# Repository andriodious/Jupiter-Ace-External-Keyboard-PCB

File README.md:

# Jupiter-Ace-External-Keyboard-PCB

Allows an external keyboard to be built for a Jupiter Ace micro. Inspiration for this board came from:
https://www.jupiter-ace.co.uk/custom_aces_CN_IBMACE.html

The measurements for this keyboard allow the fitting of Cherry Part Number: MX1A-L1NN key switches.

The board has also been fitted into a DK-Tronics keyboard case : https://t-lcarchive.org/dktronics-keyboard/

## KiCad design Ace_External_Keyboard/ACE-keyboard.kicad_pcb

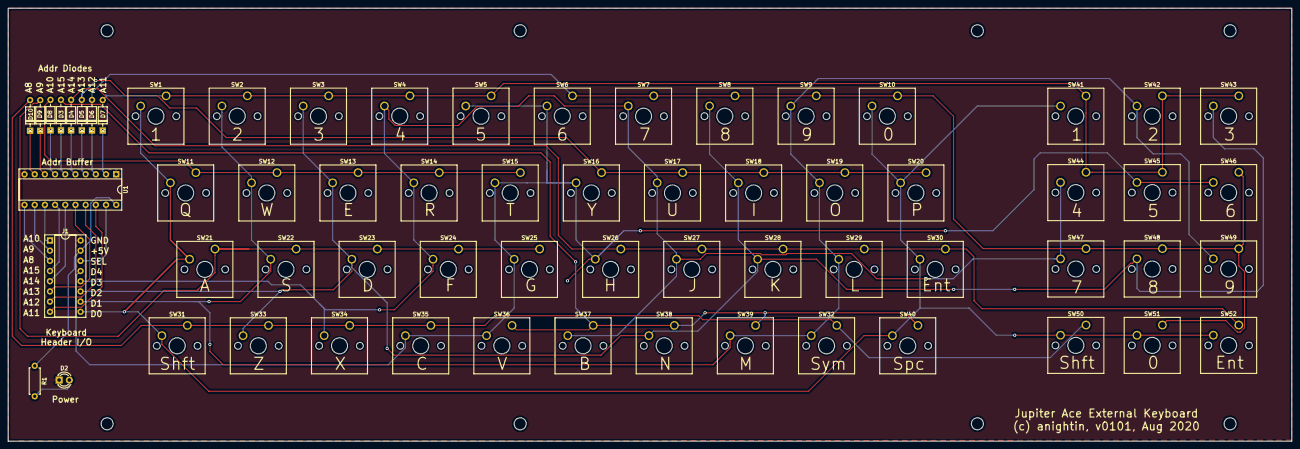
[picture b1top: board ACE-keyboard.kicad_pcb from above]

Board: 2 copper layers, 320.0 x 108.0 mm, 64 parts (0 on the bottom side), 33 nets.

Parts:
D2: LED; LED_D3.0mm
D3, D4, D5, D6, D7, D8, D9, D10: 1N4148; D_DO-35_SOD27_P7.62mm_Horizontal
J1: Keyboard_Header; DIP-16_W7.62mm_Socket
R1: 1K; R_Axial_DIN0207_L6.3mm_D2.5mm_P7.62mm_Horizontal
SW1: 1; SW_Cherry_MX1A_1.00u_PCB
SW2: 2; SW_Cherry_MX1A_1.00u_PCB
SW3: 3; SW_Cherry_MX1A_1.00u_PCB
SW4: 4; SW_Cherry_MX1A_1.00u_PCB
SW5: 5; SW_Cherry_MX1A_1.00u_PCB
SW6: 6; SW_Cherry_MX1A_1.00u_PCB
SW7: 7; SW_Cherry_MX1A_1.00u_PCB
SW8: 8; SW_Cherry_MX1A_1.00u_PCB
SW9: 9; SW_Cherry_MX1A_1.00u_PCB
SW10: 0; SW_Cherry_MX1A_1.00u_PCB
SW11: Q; SW_Cherry_MX1A_1.00u_PCB
SW12: W; SW_Cherry_MX1A_1.00u_PCB
SW13: E; SW_Cherry_MX1A_1.00u_PCB
SW14: R; SW_Cherry_MX1A_1.00u_PCB
SW15: T; SW_Cherry_MX1A_1.00u_PCB
SW16: Y; SW_Cherry_MX1A_1.00u_PCB
SW17: U; SW_Cherry_MX1A_1.00u_PCB
SW18: I; SW_Cherry_MX1A_1.00u_PCB
SW19: O; SW_Cherry_MX1A_1.00u_PCB
SW20: P; SW_Cherry_MX1A_1.00u_PCB
SW21: A; SW_Cherry_MX1A_1.00u_PCB
SW22: S; SW_Cherry_MX1A_1.00u_PCB
SW23: D; SW_Cherry_MX1A_1.00u_PCB
SW24: F; SW_Cherry_MX1A_1.00u_PCB
SW25: G; SW_Cherry_MX1A_1.00u_PCB
SW26: H; SW_Cherry_MX1A_1.00u_PCB
SW27: J; SW_Cherry_MX1A_1.00u_PCB
SW28: K; SW_Cherry_MX1A_1.00u_PCB
SW29: L; SW_Cherry_MX1A_1.00u_PCB
SW30: Enter; SW_Cherry_MX1A_1.00u_PCB
SW31: Shft; SW_Cherry_MX1A_1.00u_PCB
SW32: Ctrl; SW_Cherry_MX1A_1.00u_PCB
SW33: Z; SW_Cherry_MX1A_1.00u_PCB
SW34: X; SW_Cherry_MX1A_1.00u_PCB
SW35: C; SW_Cherry_MX1A_1.00u_PCB
SW36: V; SW_Cherry_MX1A_1.00u_PCB
SW37: B; SW_Cherry_MX1A_1.00u_PCB
SW38: N; SW_Cherry_MX1A_1.00u_PCB
SW39: M; SW_Cherry_MX1A_1.00u_PCB
SW40: Space; SW_Cherry_MX1A_1.00u_PCB
SW41: KP1; SW_Cherry_MX1A_1.00u_PCB
SW42: KP2; SW_Cherry_MX1A_1.00u_PCB
SW43: KP3; SW_Cherry_MX1A_1.00u_PCB
SW44: KP4; SW_Cherry_MX1A_1.00u_PCB
SW45: KP5; SW_Cherry_MX1A_1.00u_PCB
SW46: KP6; SW_Cherry_MX1A_1.00u_PCB
SW47: KP7; SW_Cherry_MX1A_1.00u_PCB
SW48: KP8; SW_Cherry_MX1A_1.00u_PCB
SW49: KP9; SW_Cherry_MX1A_1.00u_PCB
SW50: KPShft; SW_Cherry_MX1A_1.00u_PCB
SW51: KP0; SW_Cherry_MX1A_1.00u_PCB
SW52: KPEnter; SW_Cherry_MX1A_1.00u_PCB
U1: 74LS245; DIP-20_W7.62mm_Socket

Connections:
+5V: J1.15, R1.1, U1.20
/A8: D10.1, U1.9
/A9: D9.1, U1.8
/A10: D8.1, U1.7
/A11: D7.1, U1.2
/A12: D6.1, U1.3
/A13: D5.1, U1.4
/A14: D4.1, U1.5
/A15: D3.1, U1.6
/D0: J1.9, SW1.2, SW10.2, SW11.2, SW20.2, SW21.2, SW30.2, SW31.2, SW40.2, SW41.2, SW50.2, SW51.2, SW52.2
/D1: J1.10, SW2.2, SW9.2, SW12.2, SW19.2, SW22.2, SW29.2, SW32.2, SW39.2, SW42.2, SW49.2
/D2: J1.11, SW3.2, SW8.2, SW13.2, SW18.2, SW23.2, SW28.2, SW33.2, SW38.2, SW43.2, SW48.2
/D3: J1.12, SW4.2, SW7.2, SW14.2, SW17.2, SW24.2, SW27.2, SW34.2, SW37.2, SW44.2, SW47.2
/D4: J1.13, SW5.2, SW6.2, SW15.2, SW16.2, SW25.2, SW26.2, SW35.2, SW36.2, SW45.2, SW46.2
GND: D2.1, J1.16, U1.1, U1.10
unnamed: D2.2, R1.2
unnamed: D3.2, SW36.1, SW37.1, SW38.1, SW39.1, SW40.1
unnamed: D4.2, SW26.1, SW27.1, SW28.1, SW29.1, SW30.1, SW52.1
unnamed: D5.2, SW16.1, SW17.1, SW18.1, SW19.1, SW20.1
unnamed: D6.2, SW6.1, SW7.1, SW8.1, SW9.1, SW10.1, SW46.1, SW47.1, SW48.1, SW49.1, SW51.1
unnamed: D7.2, SW1.1, SW2.1, SW3.1, SW4.1, SW5.1, SW41.1, SW42.1, SW43.1, SW44.1, SW45.1
unnamed: D8.2, SW11.1, SW12.1, SW13.1, SW14.1, SW15.1
unnamed: D9.2, SW21.1, SW22.1, SW23.1, SW24.1, SW25.1
unnamed: D10.2, SW31.1, SW32.1, SW33.1, SW34.1, SW35.1, SW50.1
unnamed: J1.1, U1.13
unnamed: J1.2, U1.12
unnamed: J1.3, U1.11
unnamed: J1.4, U1.14
unnamed: J1.5, U1.15
unnamed: J1.6, U1.16
unnamed: J1.7, U1.17
unnamed: J1.8, U1.18
unnamed: J1.14, U1.19
